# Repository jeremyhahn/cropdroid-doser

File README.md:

# cropdroid-doser

Dosing / nutrient controller for the CropDroid automation system.

# PIN Usage

## Usable

Dosing pumps can be operated on digital pins 02, 03, 05, 06, 07, 08, 09.

## Reserved

#### Serial

Arduino communicates over serial using digital pins 00 (RX) and 01 (TX).

#### Ethernet

Arduino communicates with both the W5100 and SD card using the SPI bus (through the ICSP header).

On all boards, pin 10 is used to select the W5100 and pin 4 for the SD card. 

##### Nano / Uno
Digital pins 10, 11, 12, and 13.

##### Meta
Digital pins 50, 51, and 52. 

## Support

Please consider supporting this project for ongoing success and sustainability. I'm a passionate open source contributor making a professional living creating free, secure, scalable, robust, enterprise grade, distributed systems and cloud native solutions.

I'm also available for international consulting opportunities. Please let me know how I can assist you or your organization in achieving your desired security posture and technology goals.

https://github.com/sponsors/jeremyhahn

https://www.linkedin.com/in/jeremyhahn

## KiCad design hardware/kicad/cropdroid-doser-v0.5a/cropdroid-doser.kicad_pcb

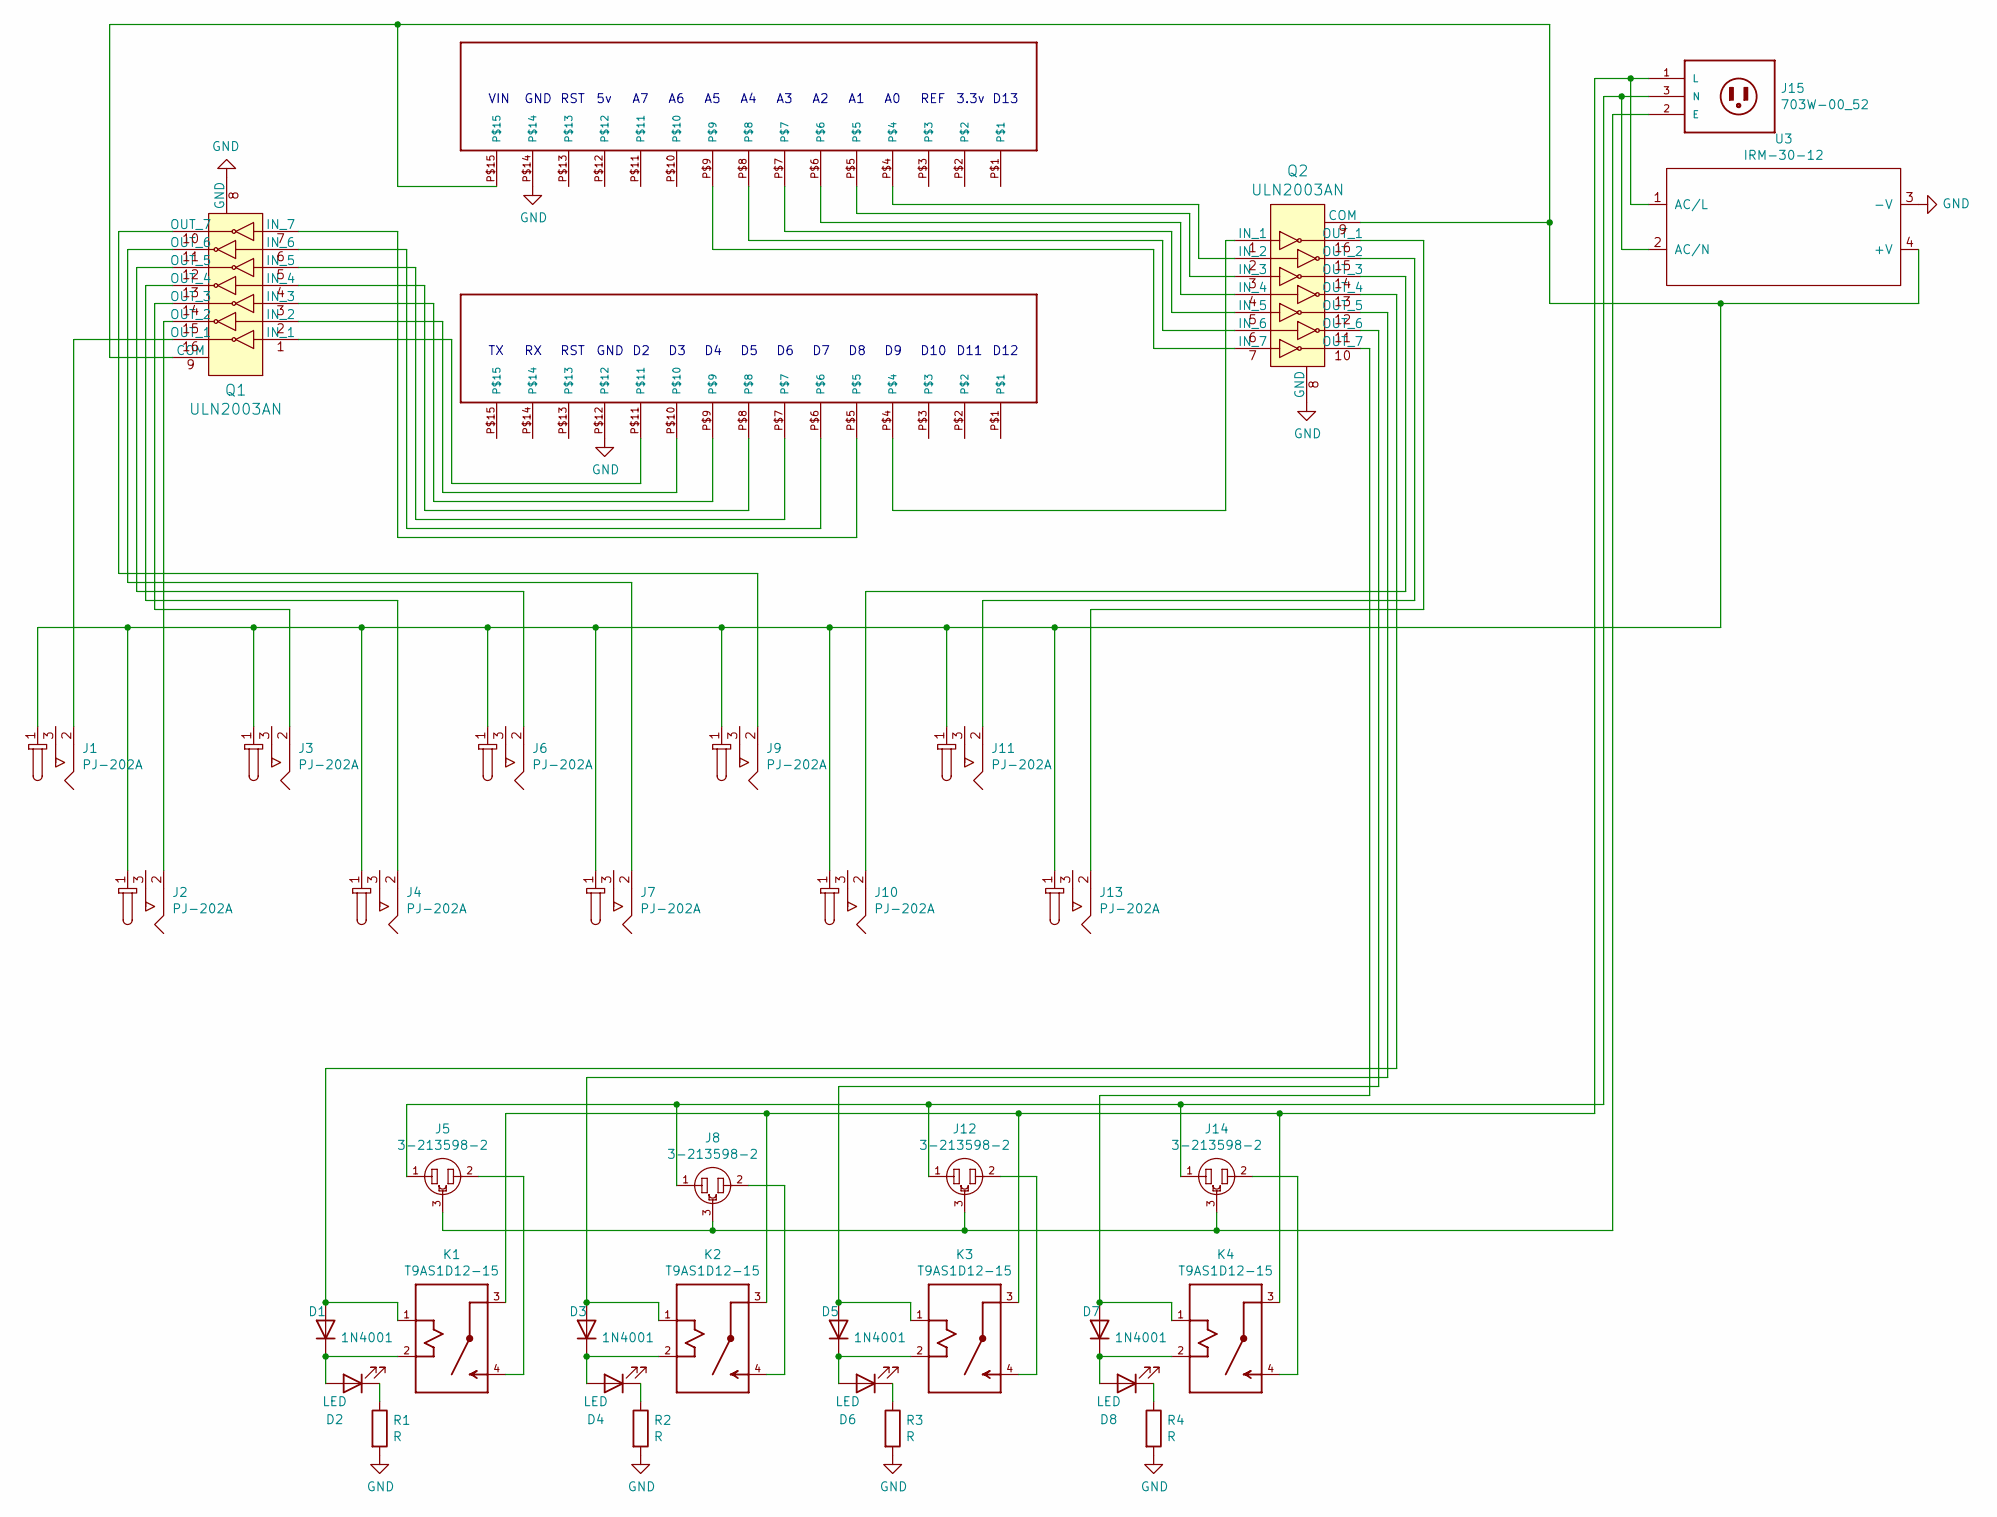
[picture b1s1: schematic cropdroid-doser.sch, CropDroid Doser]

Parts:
D1, D3, D5, D7: 1N4001; D_DO-41_SOD81_P10.16mm_Horizontal
D2, D4, D6, D8: LED; CAPPRD350W60D800H2000
J1, J2, J3, J4, J6, J7, J9, J10, J11, J13: PJ-202A; Barrel_Jack_5.5mmODx2.1mmID_PJ-202A; MPN PJ-202A; Digi-Key_PN CP-202A-ND
J5, J8, J12, J14: 3-213598-2; TE_3-213598-2
J15: 703W-00_52; QUALTEK_703W-00_52
K1, K2, K3, K4: T9AS1D12-15; RELAY_T9AS1D12-15
Q1, Q2: ULN2003AN; DIP-16_W7.62mm; MPN ULN2003AN; Digi-Key_PN 296-1979-5-ND
R1, R2, R3, R4: R; R_Axial_DIN0207_L6.3mm_D2.5mm_P10.16mm_Horizontal
U1, U2: PPTC151LFBN-RC
U3: IRM-30-12

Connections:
GND: Q1.8 (GND), Q2.8 (GND), R1.2, R2.2, R3.2, R4.2, U1.P$14, U2.P$12, U3.3 (-V)
unnamed: D1.1 (K), D2.2 (A), K1.2 (A2)
unnamed: D1.2 (A), K1.1 (A1), Q2.13 (OUT_4)
unnamed: D2.1 (K), R1.1
unnamed: D3.1 (K), D4.2 (A), K2.2 (A2)
unnamed: D3.2 (A), K2.1 (A1), Q2.12 (OUT_5)
unnamed: D4.1 (K), R2.1
unnamed: D5.1 (K), D6.2 (A), K3.2 (A2)
unnamed: D5.2 (A), K3.1 (A1), Q2.11 (OUT_6)
unnamed: D6.1 (K), R3.1
unnamed: D7.1 (K), D8.2 (A), K4.2 (A2)
unnamed: D7.2 (A), K4.1 (A1), Q2.10 (OUT_7)
unnamed: D8.1 (K), R4.1
unnamed: J1.1, J2.1, J3.1, J4.1, J6.1, J7.1, J9.1, J10.1, J11.1, J13.1, Q1.9 (COM), Q2.9 (COM), U1.P$15, U3.4 (+V)
unnamed: J1.2, Q1.16 (OUT_1)
unnamed: J2.2, Q1.15 (OUT_2)
unnamed: J3.2, Q1.14 (OUT_3)
unnamed: J4.2, Q1.13 (OUT_4)
unnamed: J5.2, K1.4 (NO)
unnamed: J6.2, Q1.12 (OUT_5)
unnamed: J7.2, Q1.11 (OUT_6)
unnamed: J8.2, K2.4 (NO)
unnamed: J9.2, Q1.10 (OUT_7)
unnamed: J10.2, Q2.14 (OUT_3)
unnamed: J11.2, Q2.15 (OUT_2)
unnamed: J5.1, J8.1, J12.1, J14.1, J15.3 (N), U3.2 (AC/N)
unnamed: J12.2, K3.4 (NO)
unnamed: J5.3, J8.3, J12.3, J14.3, J15.2 (E)
unnamed: J13.2, Q2.16 (OUT_1)
unnamed: J14.2, K4.4 (NO)
unnamed: J15.1 (L), K1.3 (C), K2.3 (C), K3.3 (C), K4.3 (C), U3.1 (AC/L)
unnamed: Q1.1 (IN_1), U2.P$11
unnamed: Q1.2 (IN_2), U2.P$10
unnamed: Q1.3 (IN_3), U2.P$9
unnamed: Q1.4 (IN_4), U2.P$8
unnamed: Q1.5 (IN_5), U2.P$7
unnamed: Q1.6 (IN_6), U2.P$6
unnamed: Q1.7 (IN_7), U2.P$5
unnamed: Q2.1 (IN_1), U2.P$4
unnamed: Q2.2 (IN_2), U1.P$4
unnamed: Q2.3 (IN_3), U1.P$5
unnamed: Q2.4 (IN_4), U1.P$6
unnamed: Q2.5 (IN_5), U1.P$7
unnamed: Q2.6 (IN_6), U1.P$8
unnamed: Q2.7 (IN_7), U1.P$9

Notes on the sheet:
RST
GND
D10
D11
D12
VIN
REF
3.3v
D13

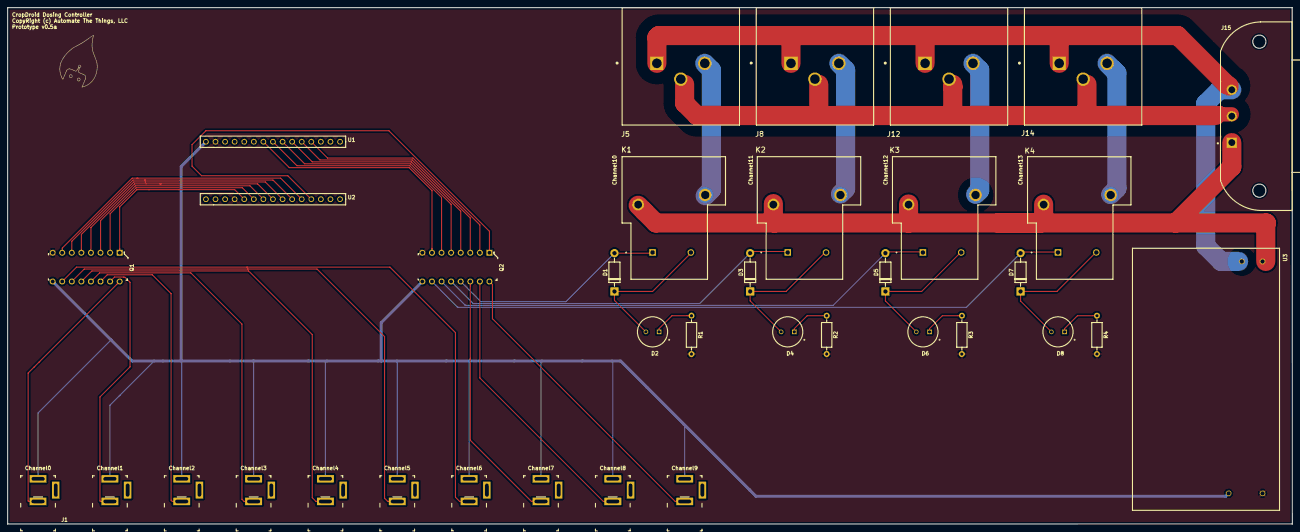
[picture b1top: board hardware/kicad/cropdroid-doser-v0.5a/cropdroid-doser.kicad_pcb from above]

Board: 2 copper layers, 340.7 x 136.9 mm, 36 parts (0 on the bottom side), 45 nets.

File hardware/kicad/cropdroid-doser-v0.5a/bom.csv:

Reference, Quantity, Value, Footprint, Datasheet, Category, DK_Datasheet_Link, DK_Detail_Page, Description, Digi-Key_PN, Family, MPN, Manufacturer, Status, Field4, Field5, Field6
D1 D3 D5 D7 ,4,"1N4001","Diode_THT:D_DO-41_SOD81_P10.16mm_Horizontal","http://www.vishay.com/docs/88503/1n4001.pdf"
D2 D4 D6 D8 ,4,"LED","libraries:CAPPRD350W60D800H2000","~"
J1 J2 J3 J4 J6 J7 J9 J10 J11 J13 ,10,"PJ-202A","digikey-footprints:Barrel_Jack_5.5mmODx2.1mmID_PJ-202A","https://www.cui.com/product/resource/digikeypdf/pj-202a.pdf","Connectors, Interconnects","https://www.cui.com/product/resource/digikeypdf/pj-202a.pdf","/product-detail/en/cui-inc/PJ-202A/CP-202A-ND/252007","CONN PWR JACK 2X5.5MM KINKED PIN","CP-202A-ND","Barrel - Power Connectors","PJ-202A","CUI Inc.","Active","","",""
J15 ,1,"703W-00_52","QUALTEK_703W-00:QUALTEK_703W-00_52","B","","","","","","","","","","Manufacturer Recommendations","Qualtek",""
J5 J8 J12 J14 ,4,"3-213598-2","3-213598-2:TE_3-213598-2","https://www.te.com/usa-en/product-3-213598-2.html?te_bu=Cor&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","","","","","","","","","","Compliant","3-213598-2","Convenience Outlet"
K1 K2 K3 K4 ,4,"T9AS1D12-15","T9AS1D12-15:RELAY_T9AS1D12-15","https://www.te.com/usa-en/product-1-1393210-4.html?te_bu=Cor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","","","","","","","","","","1-1393210-4","",""
Q1 Q2 ,2,"ULN2003AN","digikey-footprints:DIP-16_W7.62mm","http://www.ti.com/general/docs/suppproductinfo.tsp?distId=10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","Discrete Semiconductor Products","http://www.ti.com/general/docs/suppproductinfo.tsp?distId=10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","/product-detail/en/texas-instruments/ULN2003AN/296-1979-5-ND/277624","IC PWR RELAY 7NPN 1:1 16DIP","296-1979-5-ND","Transistors - Bipolar (BJT) - Arrays","ULN2003AN","Texas Instruments","Active","","",""
R1 R2 R3 R4 ,4,"R","Resistor_THT:R_Axial_DIN0207_L6.3mm_D2.5mm_P10.16mm_Horizontal","~"
U2 U1 ,2,"PPTC151LFBN-RC","PPTC151LFBN-RC:PPTC151LFBN-RC",""
U3 ,1,"IRM-30-12","IRM-30-12:IRM-30-12",""

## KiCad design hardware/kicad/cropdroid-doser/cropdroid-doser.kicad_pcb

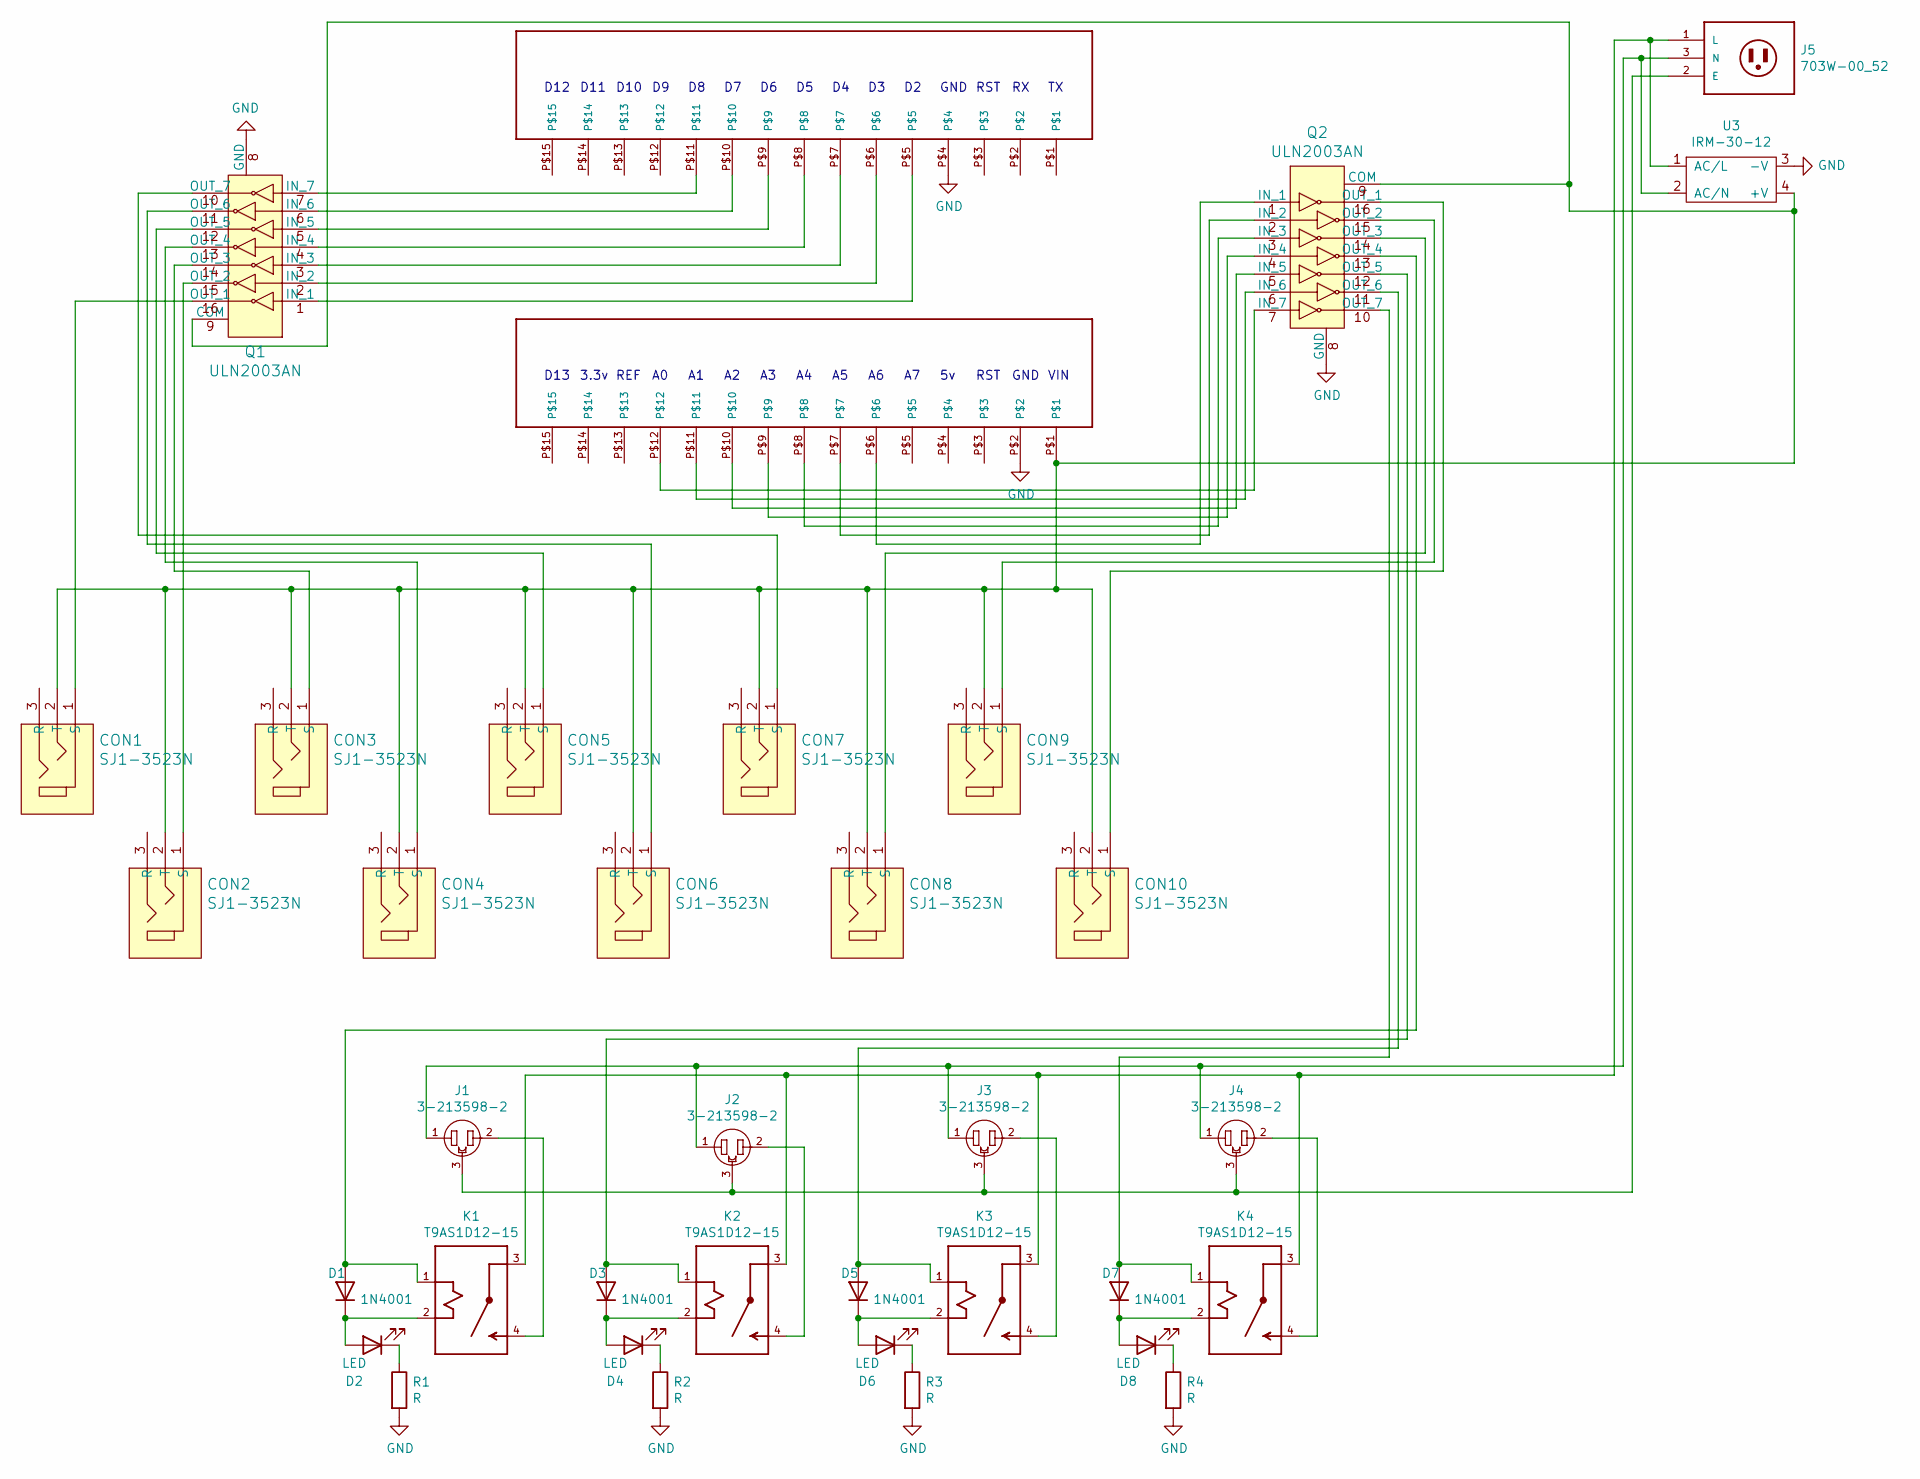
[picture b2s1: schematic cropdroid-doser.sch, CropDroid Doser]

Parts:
CON1, CON2, CON3, CON4, CON5, CON6, CON7, CON8, CON9, CON10: SJ1-3523N; Headphone_Jack_3.5mm_SJ1-3523N; MPN SJ1-3523N; Digi-Key_PN CP1-3523N-ND
D1, D3, D5, D7: 1N4001; D_DO-41_SOD81_P10.16mm_Horizontal
D2, D4, D6, D8: LED; CAPPRD350W60D800H2000
J1, J2, J3, J4: 3-213598-2; TE_3-213598-2
J5: 703W-00_52; QUALTEK_703W-00_52
K1, K2, K3, K4: T9AS1D12-15; RELAY_T9AS1D12-15
Q1, Q2: ULN2003AN; DIP-16_W7.62mm; MPN ULN2003AN; Digi-Key_PN 296-1979-5-ND
R1, R2, R3, R4: R; R_Axial_DIN0207_L6.3mm_D2.5mm_P10.16mm_Horizontal
U1, U2: PPTC151LFBN-RC
U3: IRM-30-12

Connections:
GND: Q1.8 (GND), Q2.8 (GND), R1.2, R2.2, R3.2, R4.2, U1.P$4, U2.P$2, U3.3 (-V)
unnamed: CON1.1 (S), Q1.16 (OUT_1)
unnamed: CON1.2 (T), CON2.2 (T), CON3.2 (T), CON4.2 (T), CON5.2 (T), CON6.2 (T), CON7.2 (T), CON8.2 (T), CON9.2 (T), CON10.2 (T), Q1.9 (COM), Q2.9 (COM), U2.P$1, U3.4 (+V)
unnamed: CON2.1 (S), Q1.15 (OUT_2)
unnamed: CON3.1 (S), Q1.14 (OUT_3)
unnamed: CON4.1 (S), Q1.13 (OUT_4)
unnamed: CON5.1 (S), Q1.12 (OUT_5)
unnamed: CON6.1 (S), Q1.11 (OUT_6)
unnamed: CON7.1 (S), Q1.10 (OUT_7)
unnamed: CON8.1 (S), Q2.14 (OUT_3)
unnamed: CON9.1 (S), Q2.15 (OUT_2)
unnamed: CON10.1 (S), Q2.16 (OUT_1)
unnamed: D1.1 (K), D2.2 (A), K1.2 (A2)
unnamed: D1.2 (A), K1.1 (A1), Q2.13 (OUT_4)
unnamed: D2.1 (K), R1.1
unnamed: D3.1 (K), D4.2 (A), K2.2 (A2)
unnamed: D3.2 (A), K2.1 (A1), Q2.12 (OUT_5)
unnamed: D4.1 (K), R2.1
unnamed: D5.1 (K), D6.2 (A), K3.2 (A2)
unnamed: D5.2 (A), K3.1 (A1), Q2.11 (OUT_6)
unnamed: D6.1 (K), R3.1
unnamed: D7.1 (K), D8.2 (A), K4.2 (A2)
unnamed: D7.2 (A), K4.1 (A1), Q2.10 (OUT_7)
unnamed: D8.1 (K), R4.1
unnamed: J1.1, J2.1, J3.1, J4.1, J5.3 (N), U3.2 (AC/N)
unnamed: J1.2, K1.4 (NO)
unnamed: J1.3, J2.3, J3.3, J4.3, J5.2 (E)
unnamed: J2.2, K2.4 (NO)
unnamed: J3.2, K3.4 (NO)
unnamed: J4.2, K4.4 (NO)
unnamed: J5.1 (L), K1.3 (C), K2.3 (C), K3.3 (C), K4.3 (C), U3.1 (AC/L)
unnamed: Q1.1 (IN_1), U1.P$5
unnamed: Q1.2 (IN_2), U1.P$6
unnamed: Q1.3 (IN_3), U1.P$7
unnamed: Q1.4 (IN_4), U1.P$8
unnamed: Q1.5 (IN_5), U1.P$9
unnamed: Q1.6 (IN_6), U1.P$10
unnamed: Q1.7 (IN_7), U1.P$11
unnamed: Q2.1 (IN_1), U2.P$6
unnamed: Q2.2 (IN_2), U2.P$7
unnamed: Q2.3 (IN_3), U2.P$8
unnamed: Q2.4 (IN_4), U2.P$9
unnamed: Q2.5 (IN_5), U2.P$10
unnamed: Q2.6 (IN_6), U2.P$11
unnamed: Q2.7 (IN_7), U2.P$12

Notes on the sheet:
D12
D11
D10
GND
RST
D13
3.3v
REF
VIN

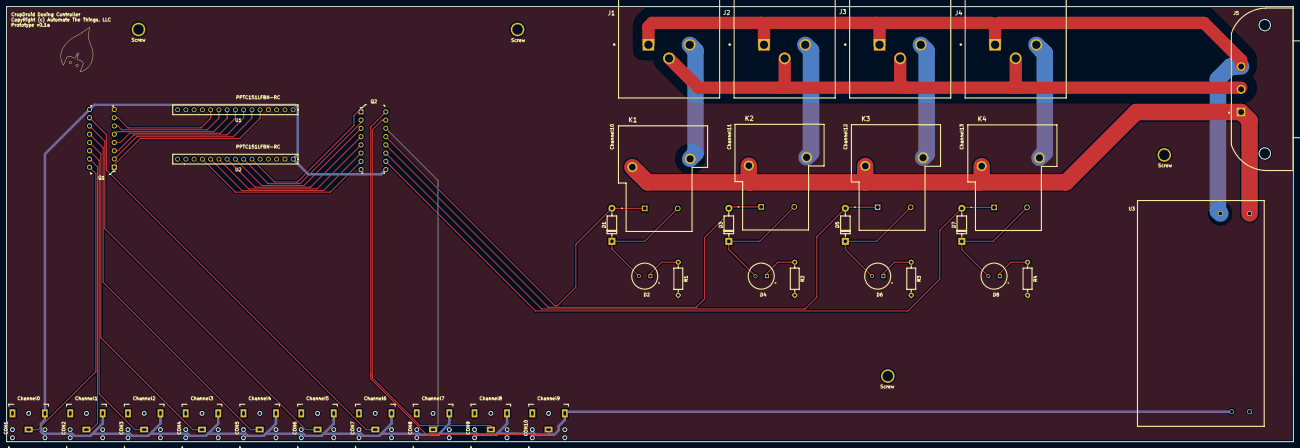
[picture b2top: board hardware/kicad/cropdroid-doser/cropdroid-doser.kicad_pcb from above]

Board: 2 copper layers, 396.1 x 133.9 mm, 40 parts (0 on the bottom side), 45 nets.

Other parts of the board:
Screw: Drill; Drill_Hole
Screw#2, Screw#3, Screw#4: Drill; Drill_Hole

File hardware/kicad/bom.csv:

Reference, Quantity, Value, Footprint, Datasheet, Category, DK_Datasheet_Link, DK_Detail_Page, Description, Digi-Key_PN, Family, MPN, Manufacturer, Status, Field4, Field5, Field6
CON1 CON2 CON3 CON5 CON6 CON8 CON9 CON10 CON4 CON7 ,10,"SJ1-3523N","digikey-footprints:Headphone_Jack_3.5mm_SJ1-3523N","https://www.cui.com/product/resource/digikeypdf/sj1-352xn_se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","Connectors, Interconnects","https://www.cui.com/product/resource/digikeypdf/sj1-352xn_se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","/product-detail/en/cui-inc/SJ1-3523N/CP1-3523N-ND/738689","CONN JACK STEREO 3.5MM R/A","CP1-3523N-ND","Barrel - Audio Connectors","SJ1-3523N","CUI Inc.","Active","","",""
D1 D3 D5 D7 ,4,"1N4001","Diode_THT:D_DO-41_SOD81_P10.16mm_Horizontal","http://www.vishay.com/docs/88503/1n4001.pdf"
D2 D4 D6 D8 ,4,"LED","libraries:CAPPRD350W60D800H2000","~"
J1 J2 J3 J4 ,4,"3-213598-2","3-213598-2:TE_3-213598-2","https://www.te.com/usa-en/product-3-213598-2.html?te_bu=Cor&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","","","","","","","","","","Compliant","3-213598-2","Convenience Outlet"
J5 ,1,"703W-00_52","QUALTEK_703W-00:QUALTEK_703W-00_52","B","","","","","","","","","","Manufacturer Recommendations","Qualtek",""
K1 K2 K3 K4 ,4,"T9AS1D12-15","T9AS1D12-15:RELAY_T9AS1D12-15","https://www.te.com/usa-en/product-1-1393210-4.html?te_bu=Cor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","","","","","","","","","","1-1393210-4","",""
Q1 Q2 ,2,"ULN2003AN","digikey-footprints:DIP-16_W7.62mm","http://www.ti.com/general/docs/suppproductinfo.tsp?distId=10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","Discrete Semiconductor Products","http://www.ti.com/general/docs/suppproductinfo.tsp?distId=10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","/product-detail/en/texas-instruments/ULN2003AN/296-1979-5-ND/277624","IC PWR RELAY 7NPN 1:1 16DIP","296-1979-5-ND","Transistors - Bipolar (BJT) - Arrays","ULN2003AN","Texas Instruments","Active","","",""
R1 R2 R3 R4 ,4,"R","Resistor_THT:R_Axial_DIN0207_L6.3mm_D2.5mm_P10.16mm_Horizontal","~"
U1 U2 ,2,"PPTC151LFBN-RC","PPTC151LFBN-RC:PPTC151LFBN-RC",""
U3 ,1,"IRM-30-12","IRM-30-12:IRM-30-12",""

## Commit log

2019-03-01 fix rest param logging
2019-03-06 add documentation. create reset endpoint
2019-03-10 use new default mac address
2019-03-10 make timer multithreaded
2019-04-05 updated to latest rest code. implement channel table
2019-04-05 fix channeol/pin mapping bug
2019-04-05 fix dispene time bug
2019-04-05 change name to cropdroid-dosing
2019-04-06 set mac address to default
2019-04-06 rename to cropdroid-room. fix channel 0 dosing bug
2019-04-11 add /stop endpoint
2019-04-11 add endpoint comments
2019-04-11 make /stop endpoint return structure compatible with /dispense
2019-04-29 add /switch endpoint
2019-06-12 fix default ip. Add EEPROM_DEBUG flag. Add EEPROM.write call
2020-02-10 add kicad project and final v0.1a artifact
2020-02-10 fix kicad nano pinout
2020-02-14 kicad doser v0.2a
2020-02-21 v0.4a hardware
2020-02-21 final v0.4a hardware
2020-02-24 fix switch endpoint
2020-03-01 update kicad cache
2020-03-02 hardware v0.5a
2020-03-11 add /sys endpoint
2020-04-13 fix /switch, /reset, and /reboot endpoints. change supported channel count to 14 (from 16)
2020-04-13 replace hard coded json syntax with global variables
2020-04-13 return metrics as array of objects
2020-04-13 fix rest resource length checks
2020-04-13 return metrics as array instead of array of objects
2020-04-30 deploy to room 2
2021-07-27 fix memory leak and channel size bug. create golang test suite
2021-09-18 bump hardware res-v0.1b and firmware v1.0.0b. add bootloader
2024-01-16 Add Makefile firmware download target. Add hardware image to README
2024-01-16 Add hardware flow image
2024-07-07 Add Fusion 360 images and source files

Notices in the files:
hardware/kicad/cropdroid-doser-v0.2a/cropdroid-doser.sch:
License: Proprietary
hardware/kicad/cropdroid-doser-v0.5a/cropdroid-doser.kicad_pcb:
CopyRight (c) Automate The Things, LLC
